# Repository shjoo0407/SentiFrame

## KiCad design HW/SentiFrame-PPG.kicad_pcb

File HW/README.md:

# HW
낙상 감지 안경의 하드웨어 — 회로, 센서 배치, 기구 설계 자료

회로도 리비전 F, 엔지니어링 시제품이다. 회로도 표제란에 "공장 검토와 벤치 테스트 필요"라고 적혀 있다.

## 구성

| 파일 | 내용 |
|---|---|
| `SentiFrame.kicad_sch`, `SentiFrame.kicad_pcb` | **메인 보드** 회로도와 PCB |
| `Circuit_01~08.kicad_sch` | 메인 보드 회로도의 하위 시트 (아래 표) |
| `SentiFrame-PPG.kicad_pro`, `.kicad_sch`, `.kicad_pcb` | **PPG 보드**(MAXM86161) 프로젝트 |
| `Catalog_01~05.kicad_sch` | 부품 카탈로그 — 연결하지 않은 부품 모음이다 ("UNWIRED - NOT FOR FABRICATION"). 메인 회로도에는 들어가지 않는다 |
| `SentiFrame_FootprintCatalog.kicad_pcb` | 풋프린트 모음 |
| `libraries/` | 프로젝트 전용 기호(`SentiFrame.kicad_sym`), 풋프린트(`SentiFrame.pretty/`), 3D 모델(`3dmodels/`) |
| `sym-lib-table`, `fp-lib-table` | 위 라이브러리를 프로젝트 폴더 기준으로 등록한 목록 |
| `SentiFrame.csv` | 부품 목록(BOM). KiCad에서 뽑은 것이라 회로도를 고치면 다시 뽑는다 |
| `assets/` | 데이터시트·제조사 자료 링크, 커패시터 DC 바이어스 특성 → [assets/README.md](assets/README.md) |
| `firmware/` | 안경 펌웨어 → [firmware/README.md](firmware/README.md), 통신 형식 → [firmware/PROTOCOL.md](firmware/PROTOCOL.md) |

메인 보드 하위 시트

| 시트 | 내용 |
|---|---|
| 01 | MCU(nRF54L15)와 2.0V 인터페이스 |
| 02 | IMU와 광학 센서 — **파일이 아직 저장소에 없다** |
| 03 | USB-C와 절연 UART 레벨 변환 |
| 04 | 충전기와 시스템 2.0V 전원 |
| 05 | PPG 5V와 보조 3V 전원 |
| 06 | SOS 버튼, LED, 진동 모터 |
| 07 | 배터리 연결과 전압 측정 |
| 08 | USB 전원 종류 감지(BC1.2, Type-C) |

## KiCad로 열기

- 파일 형식 버전이 `20260206`이다. 이 형식을 읽을 수 있는 KiCad 버전이 필요하다
- 라이브러리와 3D 모델은 프로젝트 폴더 기준(`${KIPRJMOD}`)으로 찾으므로 따로 설정하지 않아도 된다
- 메인 보드의 프로젝트 파일(`SentiFrame.kicad_pro`)이 아직 없다. 올라오기 전까지는 `.kicad_sch`·`.kicad_pcb`를 직접 열어야 하고, 넷 클래스·설계 규칙 같은 프로젝트 설정이 빠진 상태다

## 아직 저장소에 없는 것

올리는 방법은 [TODO.md](TODO.md)에 있다.

| 빠진 것 | 영향 |
|---|---|
| `Circuit_02.kicad_sch` | 메인 회로도에서 IMU·광학 센서 시트가 비어 있다 |
| `SentiFrame.kicad_pro` | 메인 보드의 프로젝트 설정이 없다. BOM에 `${EXCLUDE_FROM_POS_FILES}`가 변수 그대로 찍힌 것도 이 때문으로 보인다 |
| `firmware/boards/` | 보드 정의가 없어 저장소만으로는 펌웨어를 빌드할 수 없다 |
| `firmware/tools/` | 라즈베리파이 수신 프로그램, 기능 설정 도구, 파이썬 테스트가 쓰는 코드 |

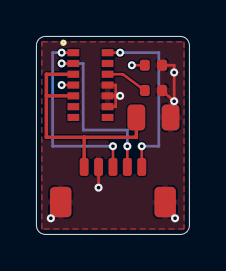
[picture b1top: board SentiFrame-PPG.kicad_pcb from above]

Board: 4 copper layers, 8.5 x 11.0 mm, 5 parts (0 on the bottom side), 7 nets.

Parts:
C7, C8: 1uF 25V X5R; C_0402_1005Metric
C9: 10uF 25V X5R; C_0805_2012Metric
J5: SM05B-SURS-TF / PPG REMOTE; JST_SUR_SM05B-SURS-TF_1x05-1MP_P0.80mm_Horizontal
U3: MAXM86161AEFD+T / 0x62; MAXM86161A_OLGA14_2.9x4.3mm

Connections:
GND: C7.2, C8.2, C9.2, J5.2, J5.MP, U3.9, U3.10, U3.11
I2C_SCL: J5.4, U3.2
I2C_SDA: J5.3, U3.1
PPG5V: C9.1, J5.1, U3.3, U3.5
PPG_INT_N: J5.5, U3.14
PPG_VLDO: C7.1, U3.4
PPG_VREF: C8.1, U3.12

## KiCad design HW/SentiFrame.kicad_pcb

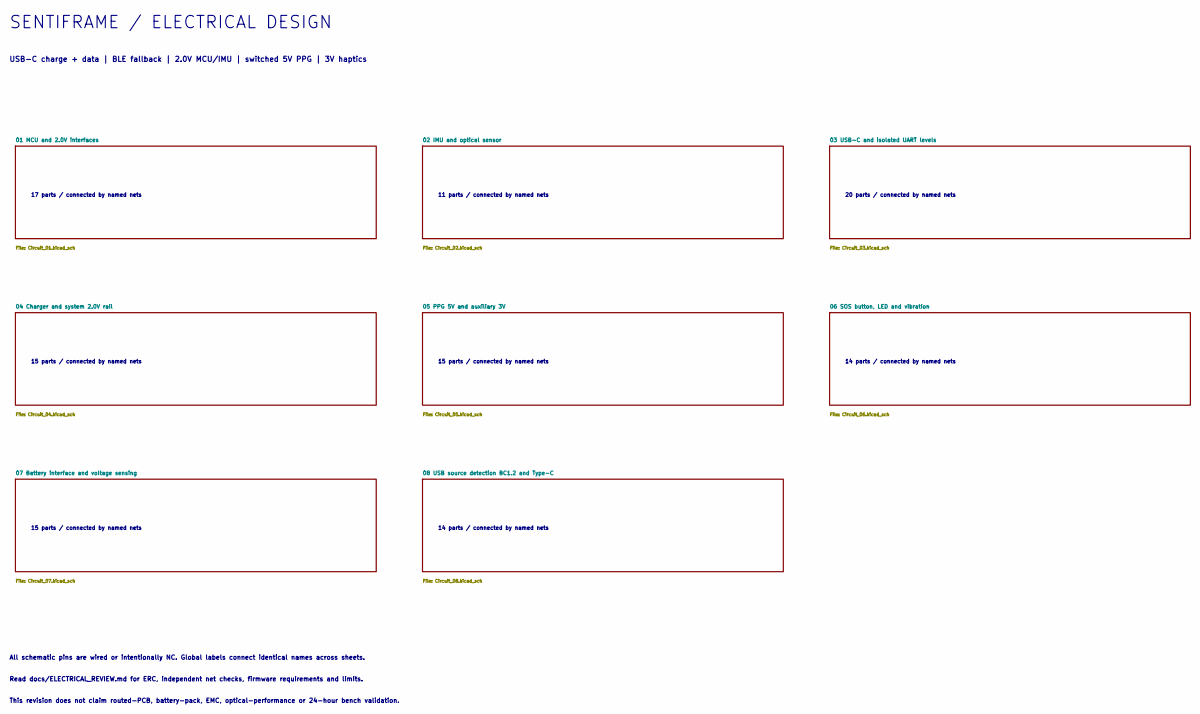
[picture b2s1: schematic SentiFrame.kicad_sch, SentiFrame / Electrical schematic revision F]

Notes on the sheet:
SENTIFRAME / ELECTRICAL DESIGN
USB-C charge + data | BLE fallback | 2.0V MCU/IMU | switched 5V PPG | 3V haptics
17 parts / connected by named nets
11 parts / connected by named nets
20 parts / connected by named nets
15 parts / connected by named nets
14 parts / connected by named nets
All schematic pins are wired or intentionally NC. Global labels connect identical names across sheets.
Read docs/ELECTRICAL_REVIEW.md for ERC, independent net checks, firmware requirements and limits.
This revision does not claim routed-PCB, battery-pack, EMC, optical-performance or 24-hour bench validation.

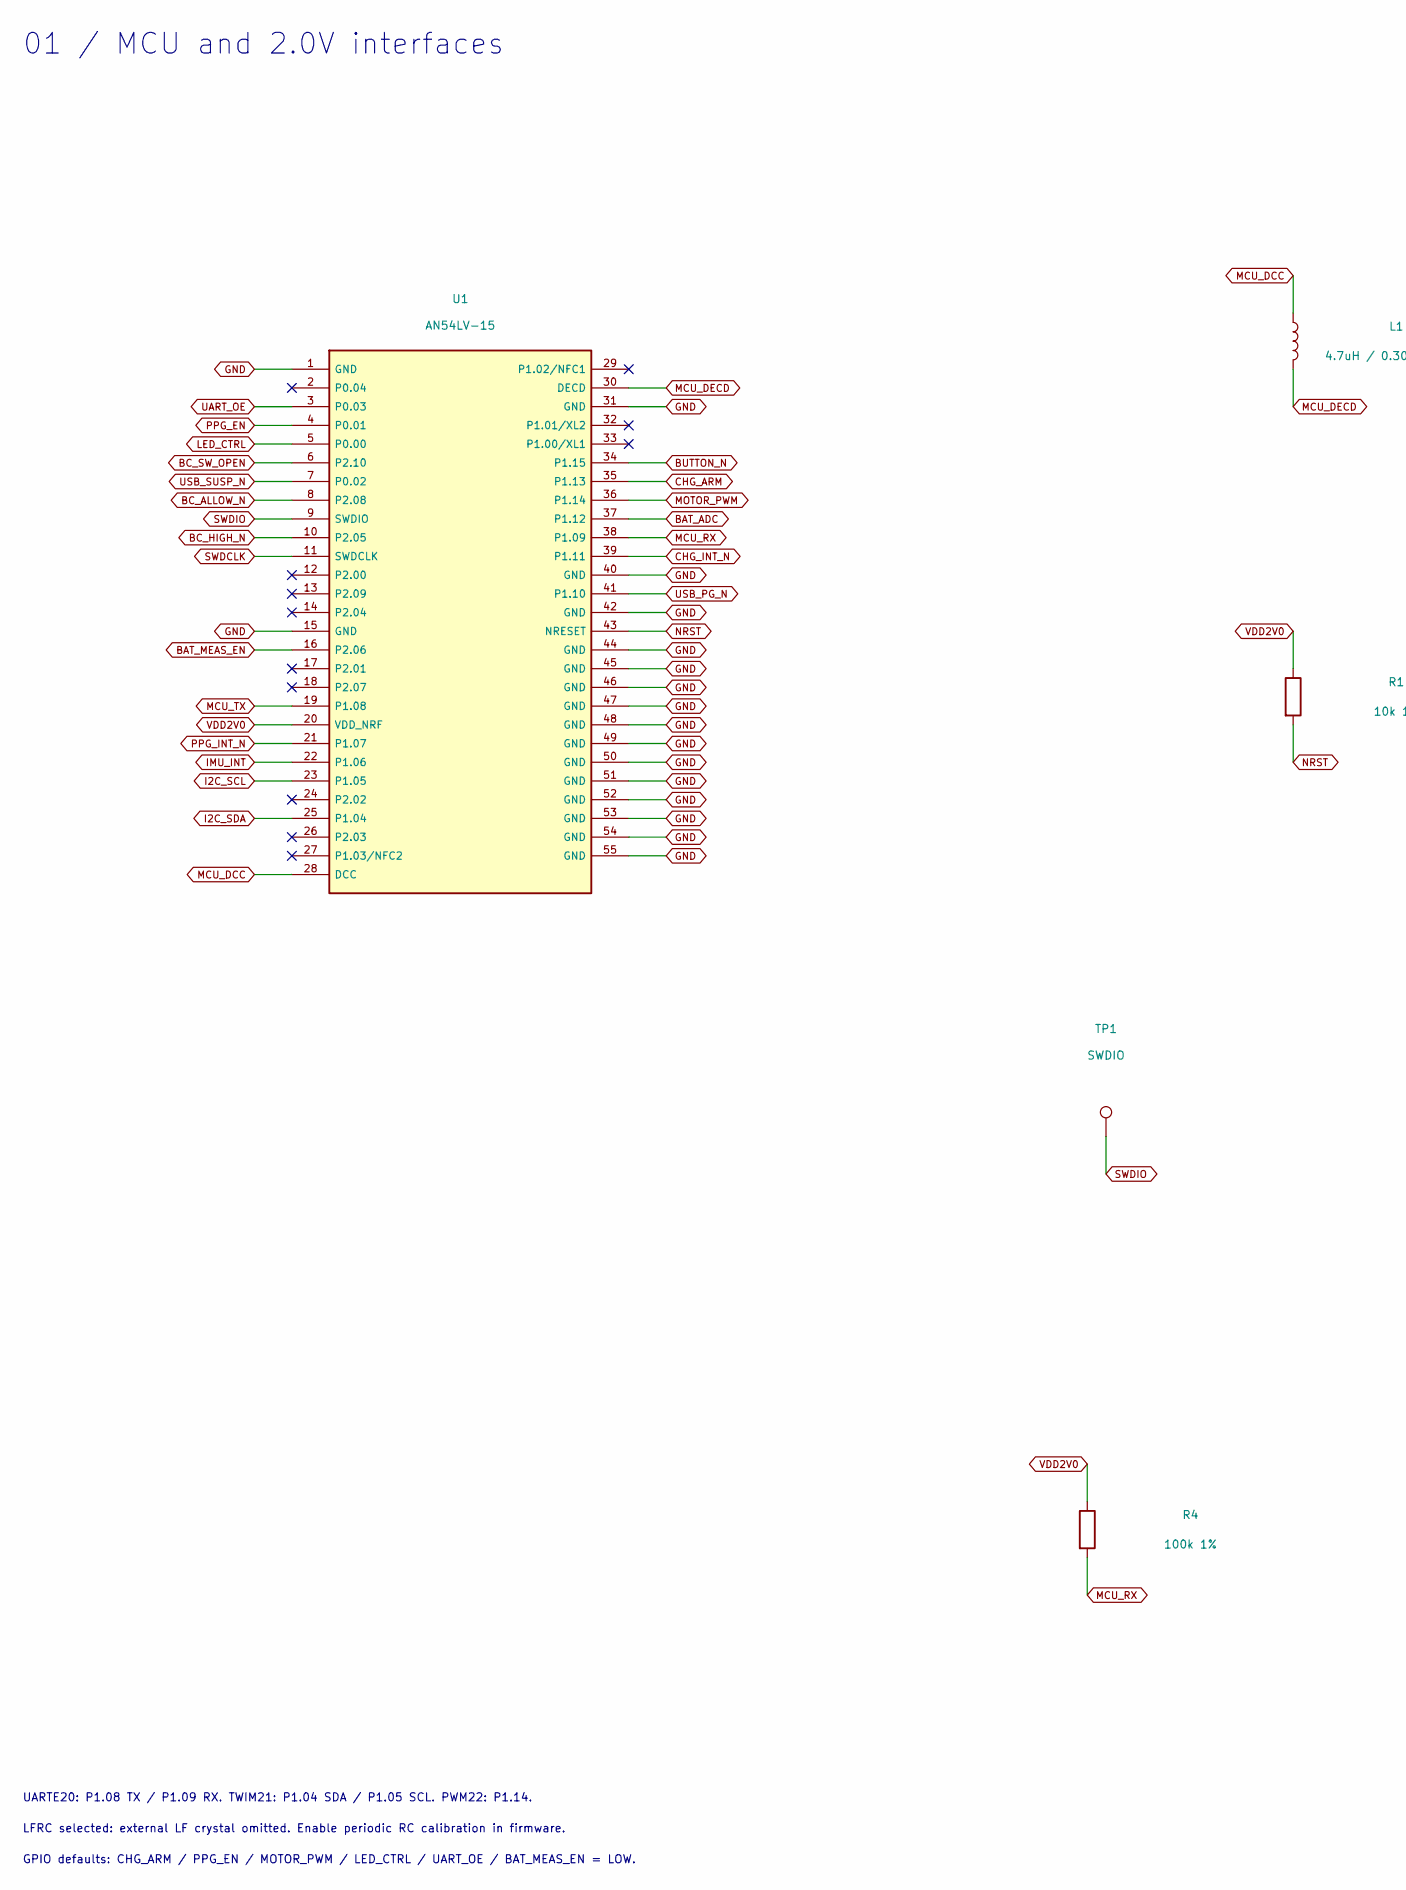
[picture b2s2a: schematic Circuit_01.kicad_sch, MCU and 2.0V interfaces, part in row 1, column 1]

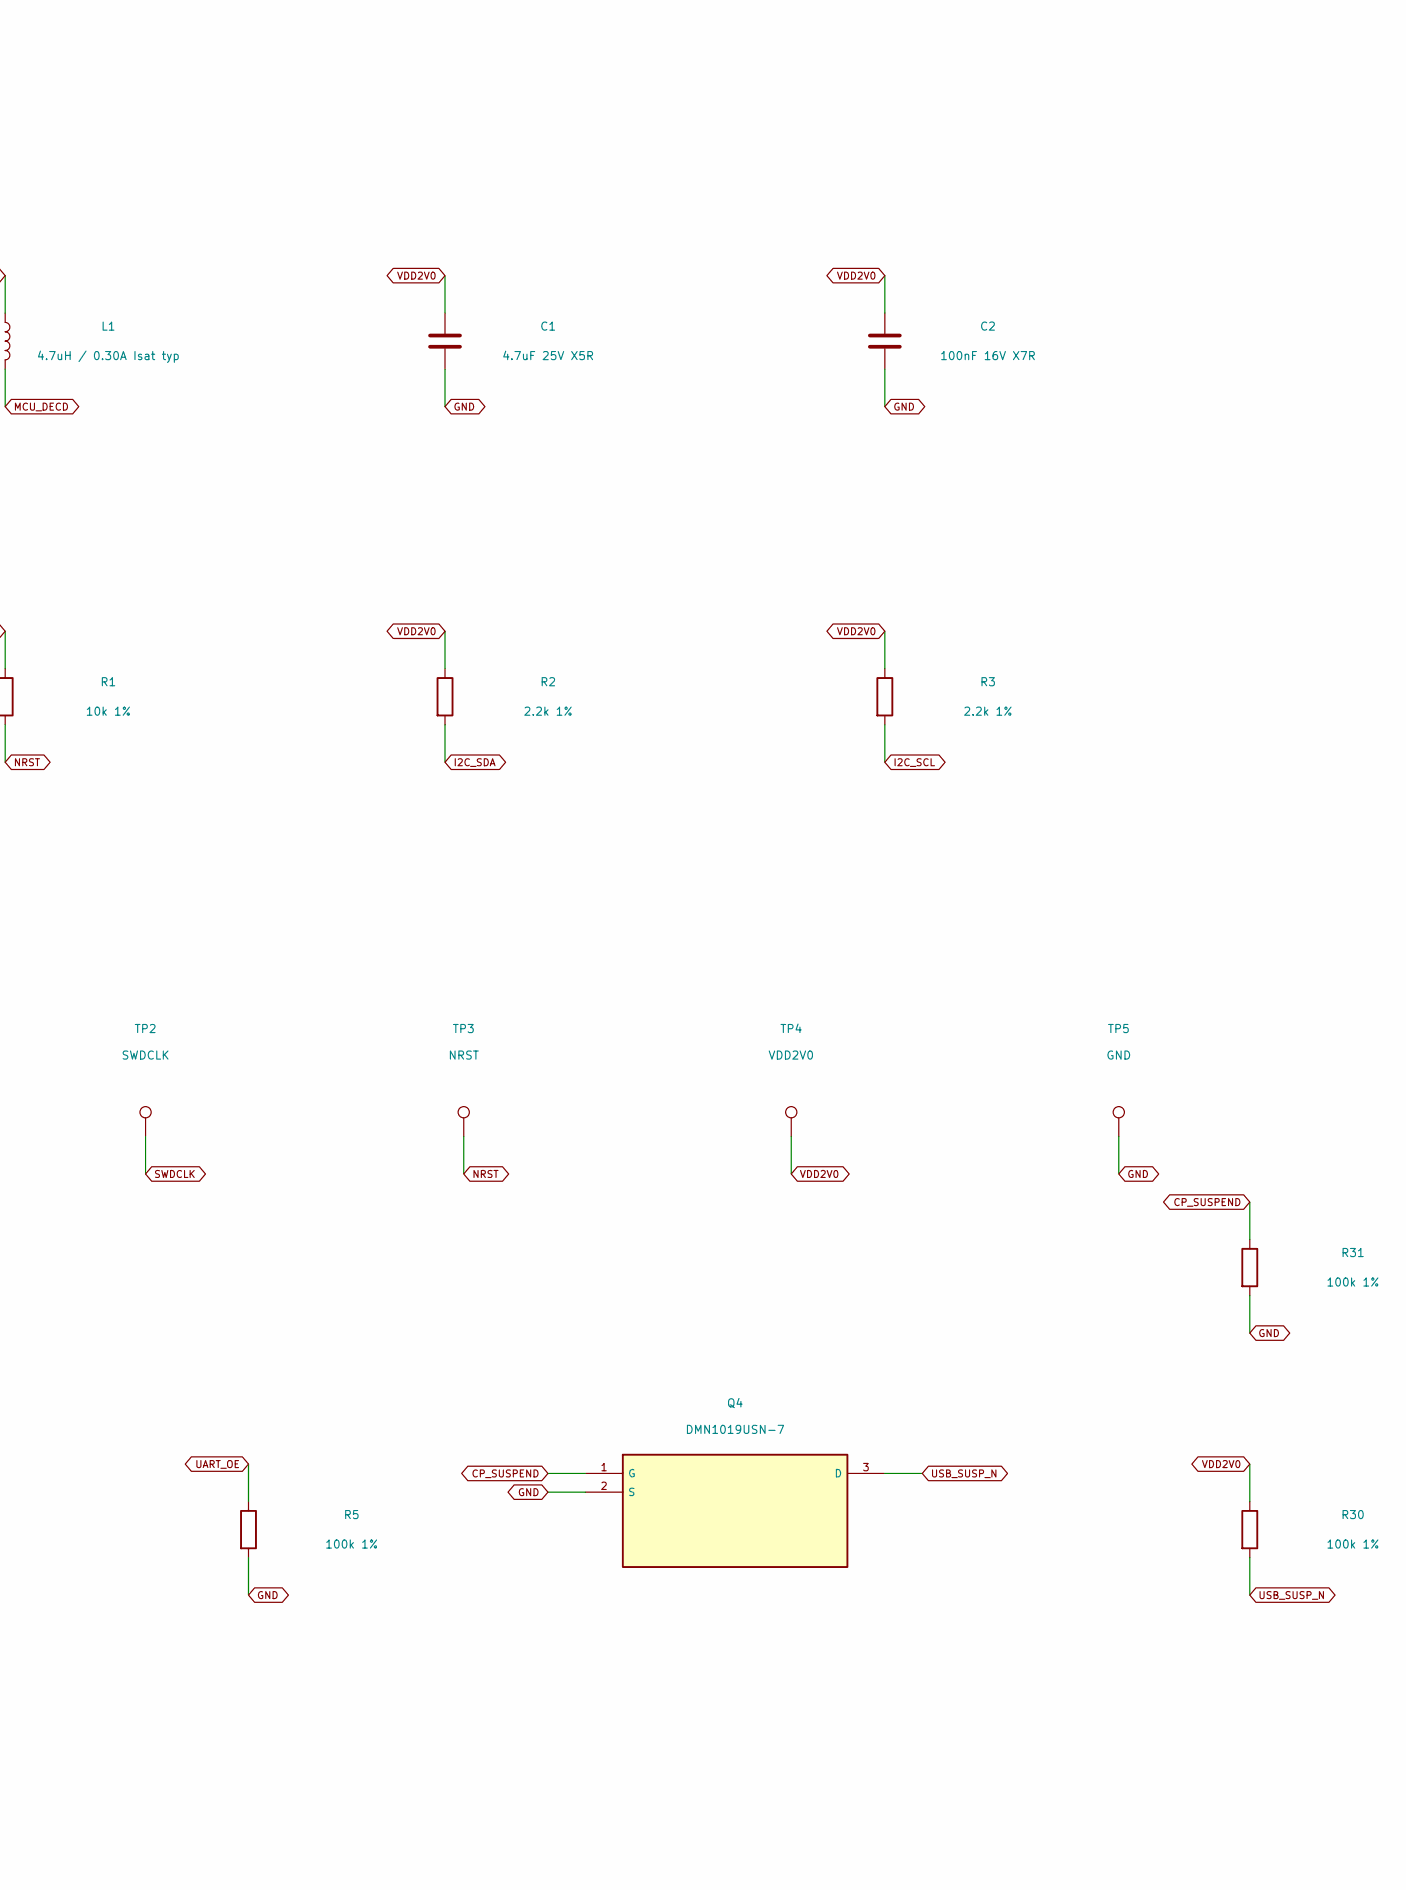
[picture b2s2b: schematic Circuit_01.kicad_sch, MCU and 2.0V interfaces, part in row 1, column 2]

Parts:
C1: 4.7uF 25V X5R; C_0603_1608Metric; MPN C1608X5R1E475K080AC
C2: 100nF 16V X7R; C_0402_1005Metric; MPN C1005X7R1C104K050BC
L1: 4.7uH / 0.30A Isat typ; L_HPC160809TF_DS; MPN HPC160809TF-4R7M
Q4: DMN1019USN-7; SC-59; MPN DMN1019USN-7
R1: 10k 1%; R_0402_1005Metric; MPN RC0402FR-0710KL
R2, R3: 2.2k 1%; R_0402_1005Metric; MPN RC0402FR-072K2L
R4, R5, R30, R31: 100k 1%; R_0402_1005Metric; MPN RC0402FR-07100KL
TP1: SWDIO; TestPoint_Pad_D1.0mm
TP2: SWDCLK; TestPoint_Pad_D1.0mm
TP3: NRST; TestPoint_Pad_D1.0mm
TP4: VDD2V0; TestPoint_Pad_D1.0mm
TP5: GND; TestPoint_Pad_D1.0mm
U1: AN54LV-15; MPN AN54LV-15

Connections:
BAT_ADC: U1.37 (P1.12); also elsewhere on the board
BAT_MEAS_EN: U1.16 (P2.06); also elsewhere on the board
BC_ALLOW_N: U1.8 (P2.08); also elsewhere on the board
BC_HIGH_N: U1.10 (P2.05); also elsewhere on the board
BC_SW_OPEN: U1.6 (P2.10); also elsewhere on the board
BUTTON_N: U1.34 (P1.15); also elsewhere on the board
CHG_ARM: U1.35 (P1.13); also elsewhere on the board
CHG_INT_N: U1.39 (P1.11); also elsewhere on the board
CP_SUSPEND: Q4.1 (G), R31.1; also elsewhere on the board
GND: C1.2, C2.2, Q4.2 (S), R5.2, R31.2, TP5.1, U1.1 (GND), U1.15 (GND), U1.31 (GND), U1.40 (GND), U1.42 (GND), U1.44 (GND), U1.45 (GND), U1.46 (GND), U1.47 (GND), U1.48 (GND), U1.49 (GND), U1.50 (GND), U1.51 (GND), U1.52 (GND), U1.53 (GND), U1.54 (GND), U1.55 (GND); also elsewhere on the board
I2C_SCL: R3.2, U1.23 (P1.05); also elsewhere on the board
I2C_SDA: R2.2, U1.25 (P1.04); also elsewhere on the board
IMU_INT: U1.22 (P1.06); also elsewhere on the board
LED_CTRL: U1.5 (P0.00); also elsewhere on the board
MCU_DCC: L1.1, U1.28 (DCC)
MCU_DECD: L1.2, U1.30 (DECD)
MCU_RX: R4.2, U1.38 (P1.09); also elsewhere on the board
MCU_TX: U1.19 (P1.08); also elsewhere on the board
MOTOR_PWM: U1.36 (P1.14); also elsewhere on the board
NRST: R1.2, TP3.1, U1.43 (NRESET)
PPG_EN: U1.4 (P0.01); also elsewhere on the board
PPG_INT_N: U1.21 (P1.07); also elsewhere on the board
SWDCLK: TP2.1, U1.11 (SWDCLK)
SWDIO: TP1.1, U1.9 (SWDIO)
UART_OE: R5.1, U1.3 (P0.03); also elsewhere on the board
USB_PG_N: U1.41 (P1.10); also elsewhere on the board
USB_SUSP_N: Q4.3 (D), R30.2, U1.7 (P0.02)
VDD2V0: C1.1, C2.1, R1.1, R2.1, R3.1, R4.1, R30.1, TP4.1, U1.20 (VDD_NRF); also elsewhere on the board

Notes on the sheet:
01 / MCU and 2.0V interfaces
UARTE20: P1.08 TX / P1.09 RX. TWIM21: P1.04 SDA / P1.05 SCL. PWM22: P1.14.
LFRC selected: external LF crystal omitted. Enable periodic RC calibration in firmware.
GPIO defaults: CHG_ARM / PPG_EN / MOTOR_PWM / LED_CTRL / UART_OE / BAT_MEAS_EN = LOW.

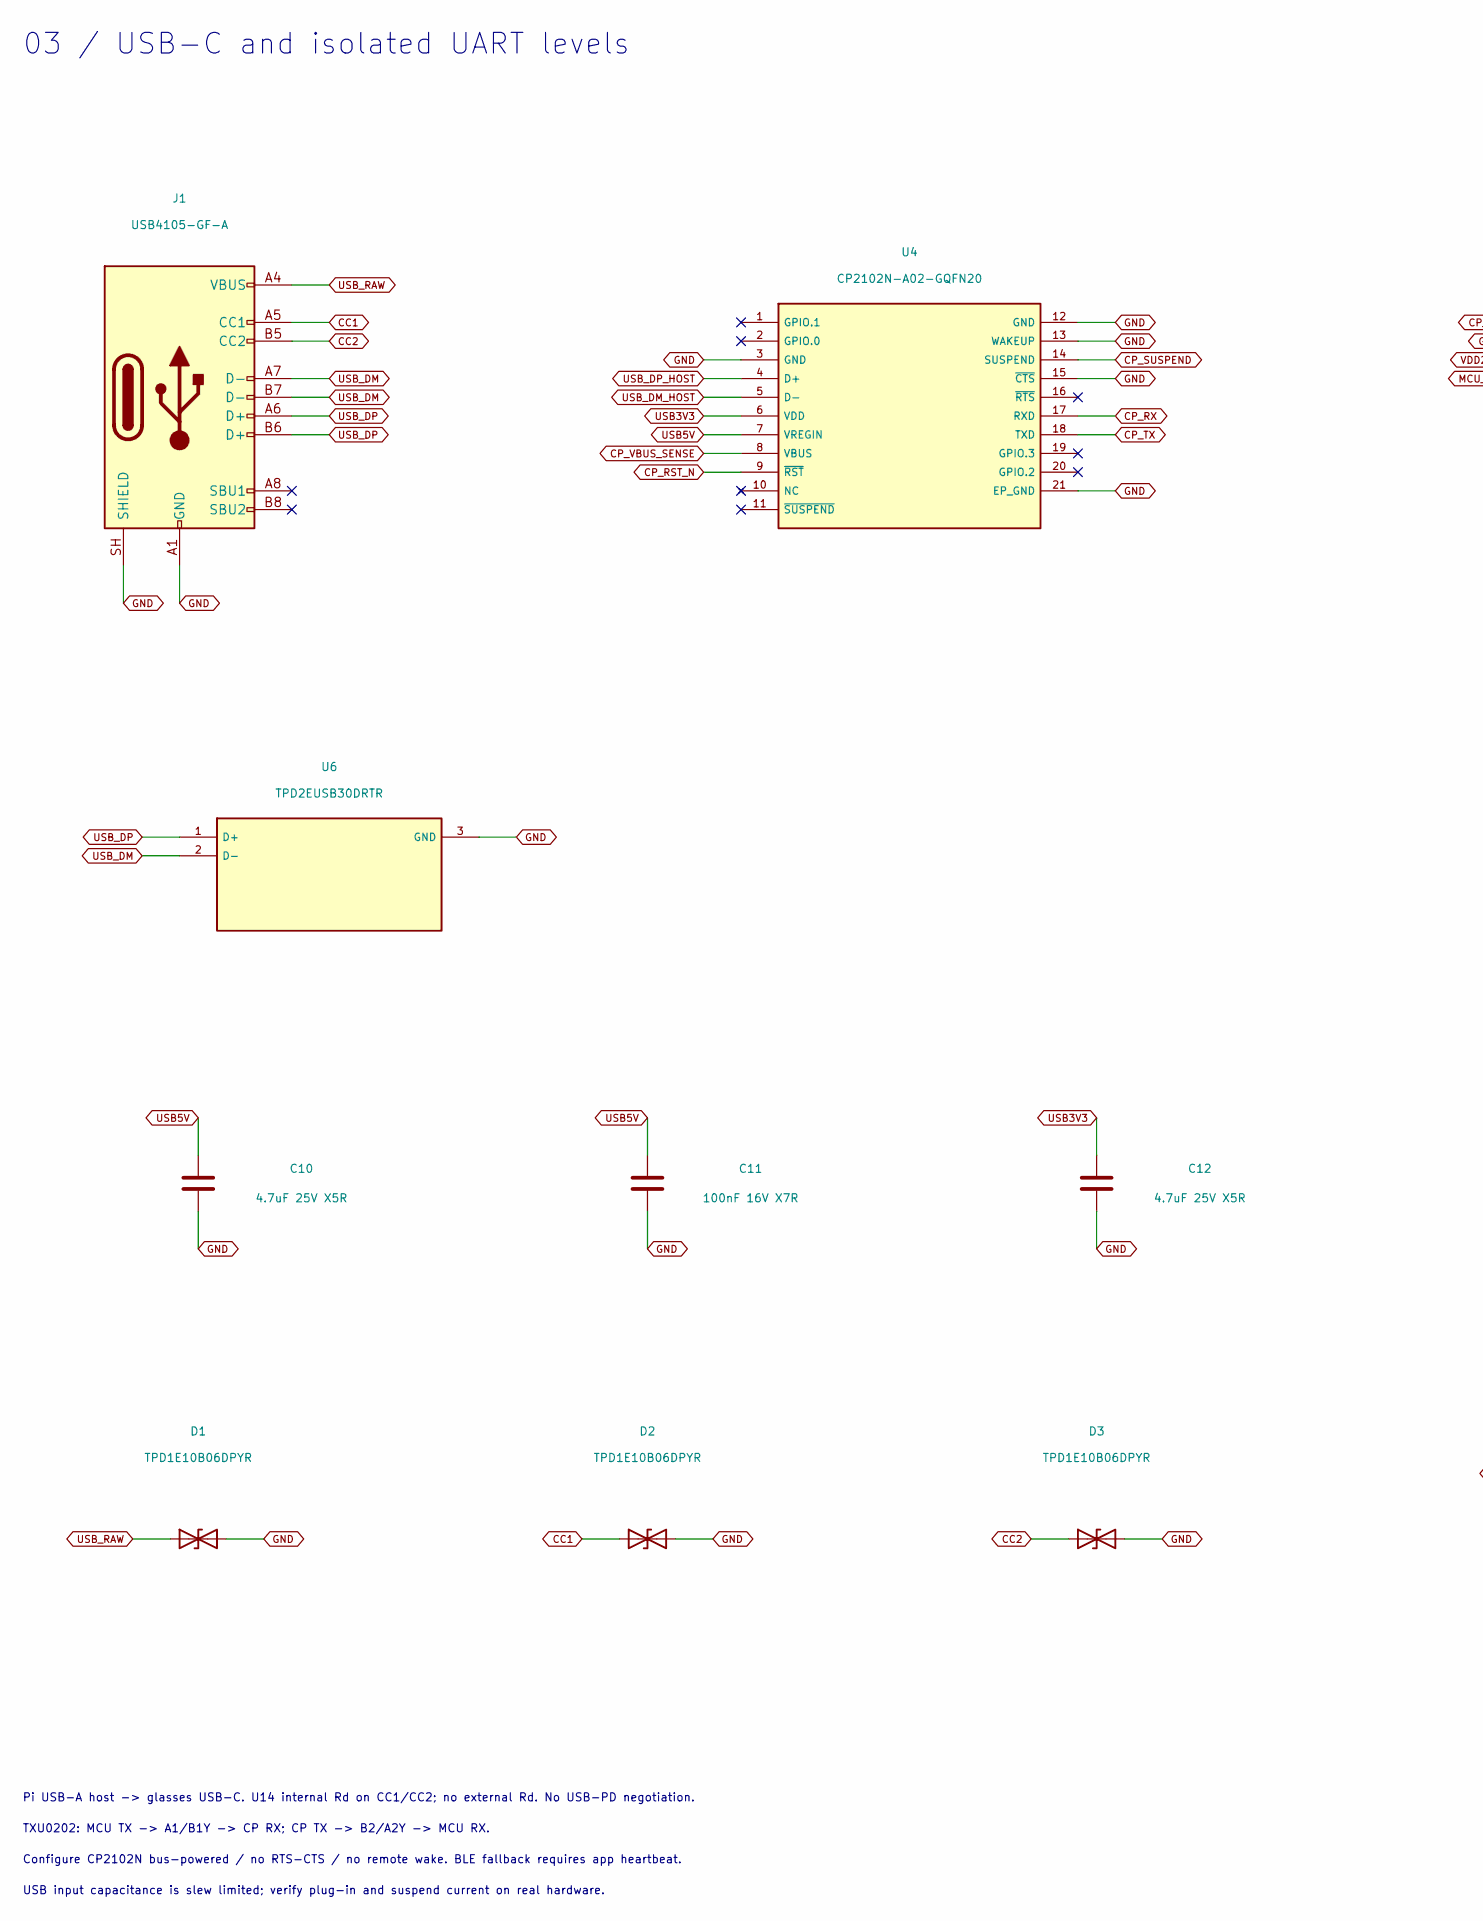
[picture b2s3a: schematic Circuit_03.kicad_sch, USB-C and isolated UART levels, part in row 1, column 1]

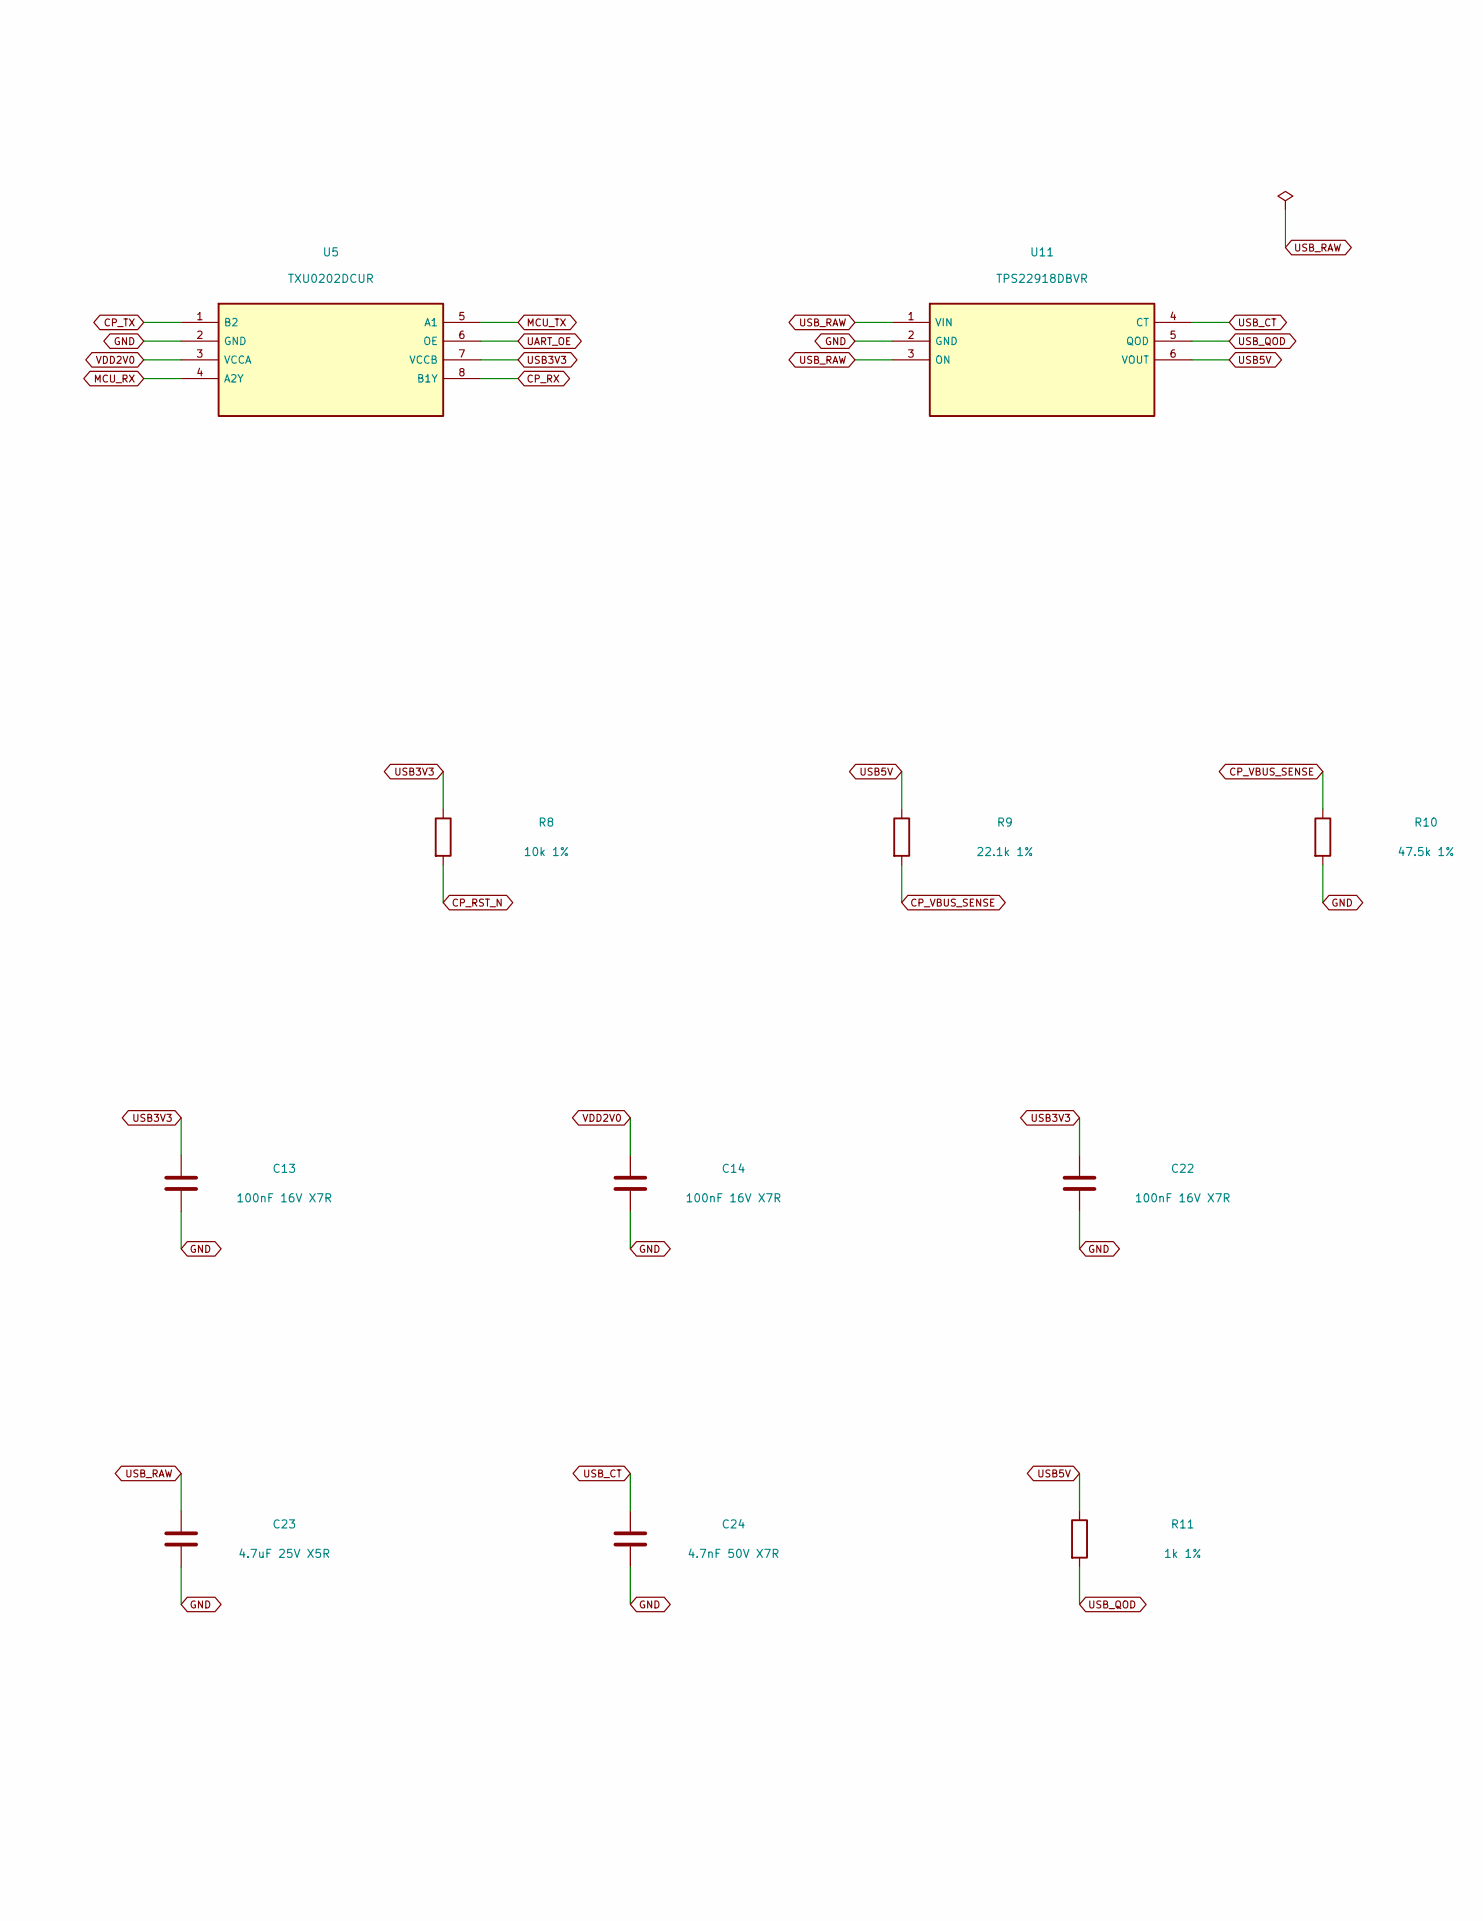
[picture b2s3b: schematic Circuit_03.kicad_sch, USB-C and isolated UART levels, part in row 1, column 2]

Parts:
C10, C12, C23: 4.7uF 25V X5R; C_0603_1608Metric; MPN C1608X5R1E475K080AC
C11, C13, C14, C22: 100nF 16V X7R; C_0402_1005Metric; MPN C1005X7R1C104K050BC
C24: 4.7nF 50V X7R; C_0402_1005Metric; MPN C1005X7R1H472K050BA
D1, D2, D3: TPD1E10B06DPYR; D_SOD-523; MPN TPD1E10B06DPYR
J1: USB4105-GF-A; USB_C_Receptacle_GCT_USB4105-xx-A_16P_TopMnt_Horizontal; MPN USB4105-GF-A
R8: 10k 1%; R_0402_1005Metric; MPN RC0402FR-0710KL
R9: 22.1k 1%; R_0402_1005Metric; MPN RC0402FR-0722K1L
R10: 47.5k 1%; R_0402_1005Metric; MPN RC0402FR-0747K5L
R11: 1k 1%; R_0402_1005Metric; MPN RC0402FR-071KL
U4: CP2102N-A02-GQFN20; SiliconLabs_QFN-20-1EP_3x3mm_P0.5mm_EP1.8x1.8mm; MPN CP2102N-A02-GQFN20
U5: TXU0202DCUR; VSSOP-8_2.3x2mm_P0.5mm; MPN TXU0202DCUR
U6: TPD2EUSB30DRTR; Texas_DRT-3; MPN TPD2EUSB30DRTR
U11: TPS22918DBVR; SOT-23-6; MPN TPS22918DBVR

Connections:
CC1: D2.1 (A1), J1.A5 (CC1); also elsewhere on the board
CC2: D3.1 (A1), J1.B5 (CC2); also elsewhere on the board
CP_RST_N: R8.2, U4.9 (~RST)
CP_RX: U4.17 (RXD), U5.8 (B1Y)
CP_SUSPEND: U4.14 (SUSPEND); also elsewhere on the board
CP_TX: U4.18 (TXD), U5.1 (B2)
CP_VBUS_SENSE: R9.2, R10.1, U4.8 (VBUS)
GND: C10.2, C11.2, C12.2, C13.2, C14.2, C22.2, C23.2, C24.2, D1.2 (A2), D2.2 (A2), D3.2 (A2), J1.A1 (GND), J1.A12 (GND), J1.B1 (GND), J1.B12 (GND), J1.SH (SHIELD), R10.2, U4.3 (GND), U4.12 (GND), U4.13 (WAKEUP), U4.15 (~CTS), U4.21 (EP_GND), U5.2 (GND), U6.3 (GND), U11.2 (GND); also elsewhere on the board
MCU_RX: U5.4 (A2Y); also elsewhere on the board
MCU_TX: U5.5 (A1); also elsewhere on the board
UART_OE: U5.6 (OE); also elsewhere on the board
USB3V3: C12.1, C13.1, C22.1, R8.1, U4.6 (VDD), U5.7 (VCCB); also elsewhere on the board
USB5V: C10.1, C11.1, R9.1, R11.1, U4.7 (VREGIN), U11.6 (VOUT); also elsewhere on the board
USB_CT: C24.1, U11.4 (CT)
USB_DM: J1.A7 (D-), J1.B7 (D-), U6.2 (D-); also elsewhere on the board
USB_DM_HOST: U4.5 (D-); also elsewhere on the board
USB_DP: J1.A6 (D+), J1.B6 (D+), U6.1 (D+); also elsewhere on the board
USB_DP_HOST: U4.4 (D+); also elsewhere on the board
USB_QOD: R11.2, U11.5 (QOD)
USB_RAW: C23.1, D1.1 (A1), J1.A4 (VBUS), J1.A9 (VBUS), J1.B4 (VBUS), J1.B9 (VBUS), U11.1 (VIN), U11.3 (ON); also elsewhere on the board
VDD2V0: C14.1, U5.3 (VCCA); also elsewhere on the board

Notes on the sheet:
03 / USB-C and isolated UART levels
Pi USB-A host -> glasses USB-C. U14 internal Rd on CC1/CC2; no external Rd. No USB-PD negotiation.
TXU0202: MCU TX -> A1/B1Y -> CP RX; CP TX -> B2/A2Y -> MCU RX.
Configure CP2102N bus-powered / no RTS-CTS / no remote wake. BLE fallback requires app heartbeat.
USB input capacitance is slew limited; verify plug-in and suspend current on real hardware.

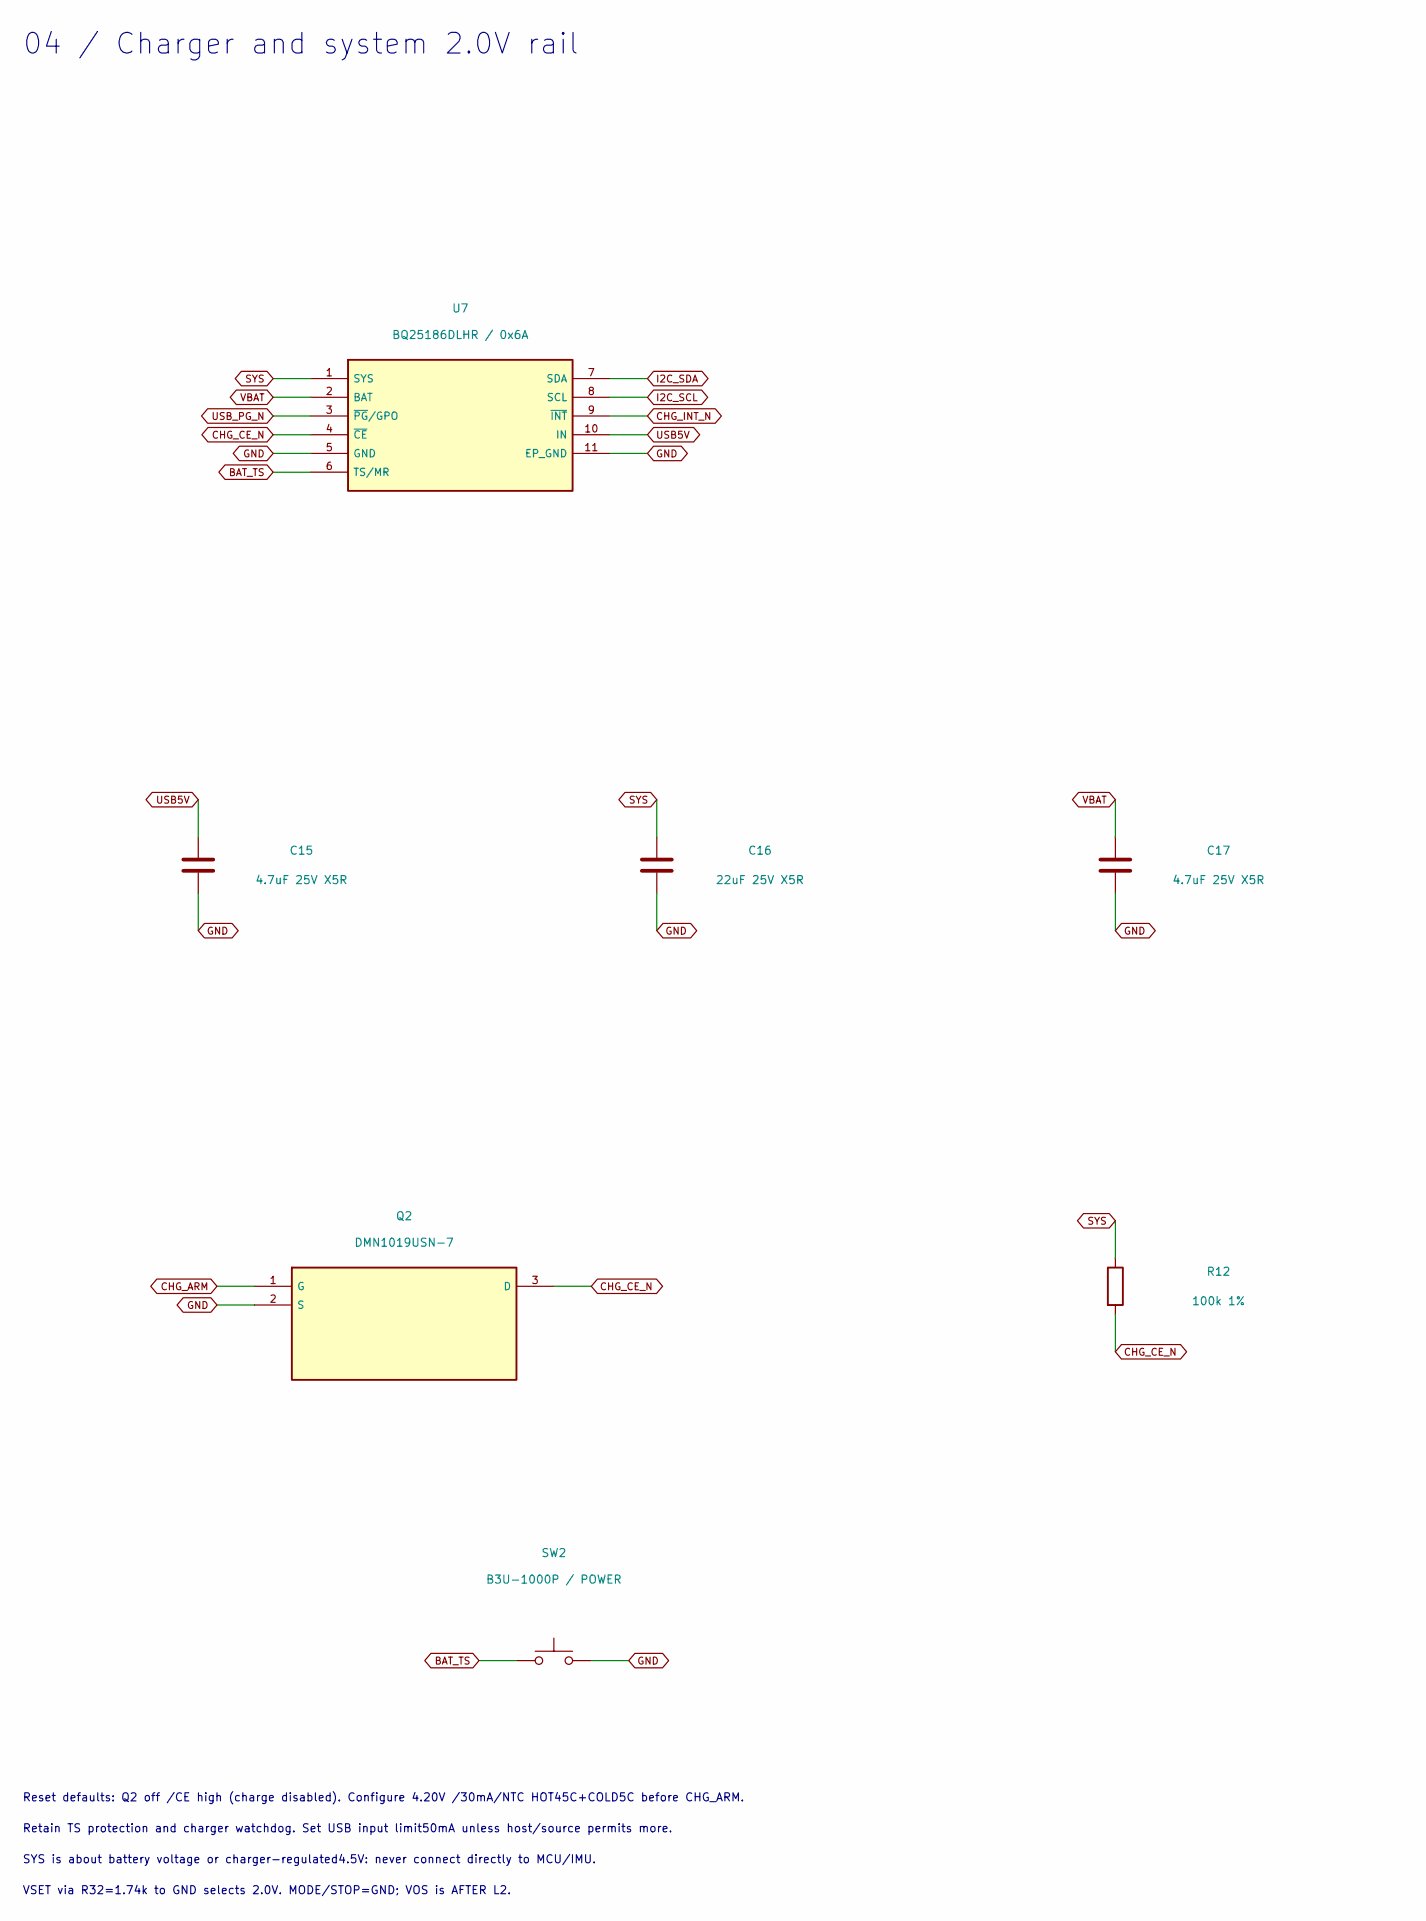
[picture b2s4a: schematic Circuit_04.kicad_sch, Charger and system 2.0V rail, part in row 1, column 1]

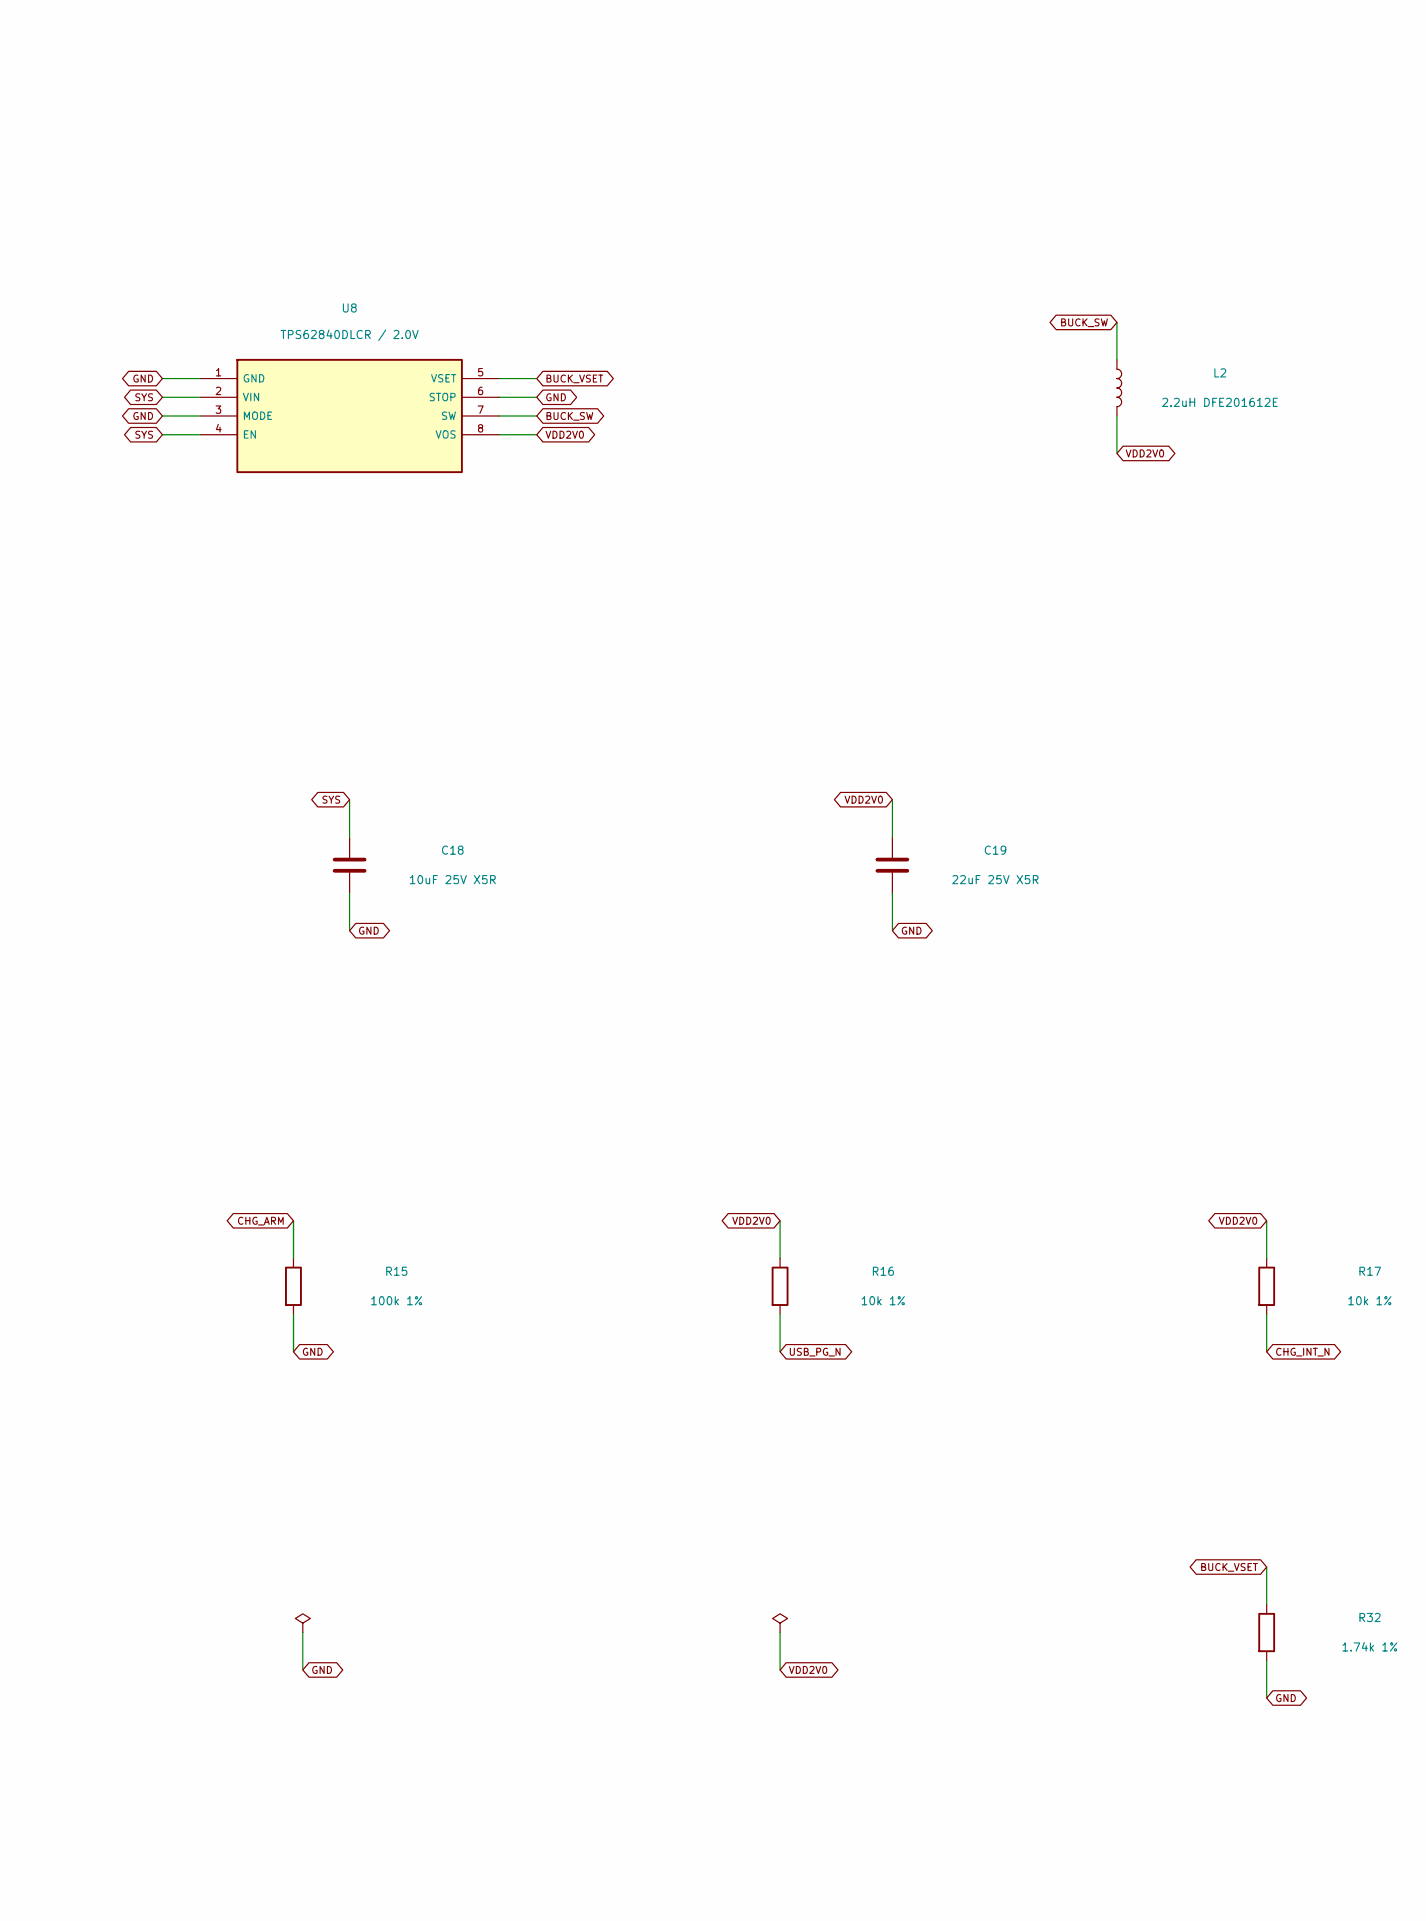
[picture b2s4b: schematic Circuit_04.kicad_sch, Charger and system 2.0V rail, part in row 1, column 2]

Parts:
C15, C17: 4.7uF 25V X5R; C_0603_1608Metric; MPN C1608X5R1E475K080AC
C16, C19: 22uF 25V X5R; C_0805_2012Metric; MPN C2012X5R1E226M125AC
C18: 10uF 25V X5R; C_0805_2012Metric; MPN C2012X5R1E106K125AB
L2: 2.2uH DFE201612E; L_DFE201612E_DS; MPN DFE201612E-2R2M=P2
Q2: DMN1019USN-7; SC-59; MPN DMN1019USN-7
R12, R15: 100k 1%; R_0402_1005Metric; MPN RC0402FR-07100KL
R16, R17: 10k 1%; R_0402_1005Metric; MPN RC0402FR-0710KL
R32: 1.74k 1%; R_0402_1005Metric; MPN RC0402FR-071K74L
SW2: B3U-1000P / POWER; SW_SPST_B3U-1000P; MPN B3U-1000P
U7: BQ25186DLHR / 0x6A; Texas_DLH0010A_WSON-10-1EP_2.2x2mm_P0.4mm_EP0.9x1.5mm; MPN BQ25186DLHR
U8: TPS62840DLCR / 2.0V; Texas_VSON-HR-8_1.5x2mm_P0.5mm; MPN TPS62840DLCR

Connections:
BAT_TS: SW2.1, U7.6 (TS/MR); also elsewhere on the board
BUCK_SW: L2.1, U8.7 (SW)
BUCK_VSET: R32.1, U8.5 (VSET)
CHG_ARM: Q2.1 (G), R15.1; also elsewhere on the board
CHG_CE_N: Q2.3 (D), R12.2, U7.4 (~CE)
CHG_INT_N: R17.2, U7.9 (~INT); also elsewhere on the board
GND: C15.2, C16.2, C17.2, C18.2, C19.2, Q2.2 (S), R15.2, R32.2, SW2.2, U7.5 (GND), U7.11 (EP_GND), U8.1 (GND), U8.3 (MODE), U8.6 (STOP); also elsewhere on the board
I2C_SCL: U7.8 (SCL); also elsewhere on the board
I2C_SDA: U7.7 (SDA); also elsewhere on the board
SYS: C16.1, C18.1, R12.1, U7.1 (SYS), U8.2 (VIN), U8.4 (EN); also elsewhere on the board
USB5V: C15.1, U7.10 (IN); also elsewhere on the board
USB_PG_N: R16.2, U7.3 (~PG/GPO); also elsewhere on the board
VBAT: C17.1, U7.2 (BAT); also elsewhere on the board
VDD2V0: C19.1, L2.2, R16.1, R17.1, U8.8 (VOS); also elsewhere on the board

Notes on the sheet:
04 / Charger and system 2.0V rail
Reset defaults: Q2 off /CE high (charge disabled). Configure 4.20V /30mA/NTC HOT45C+COLD5C before CHG_ARM.
Retain TS protection and charger watchdog. Set USB input limit50mA unless host/source permits more.
SYS is about battery voltage or charger-regulated4.5V: never connect directly to MCU/IMU.
VSET via R32=1.74k to GND selects 2.0V. MODE/STOP=GND; VOS is AFTER L2.
